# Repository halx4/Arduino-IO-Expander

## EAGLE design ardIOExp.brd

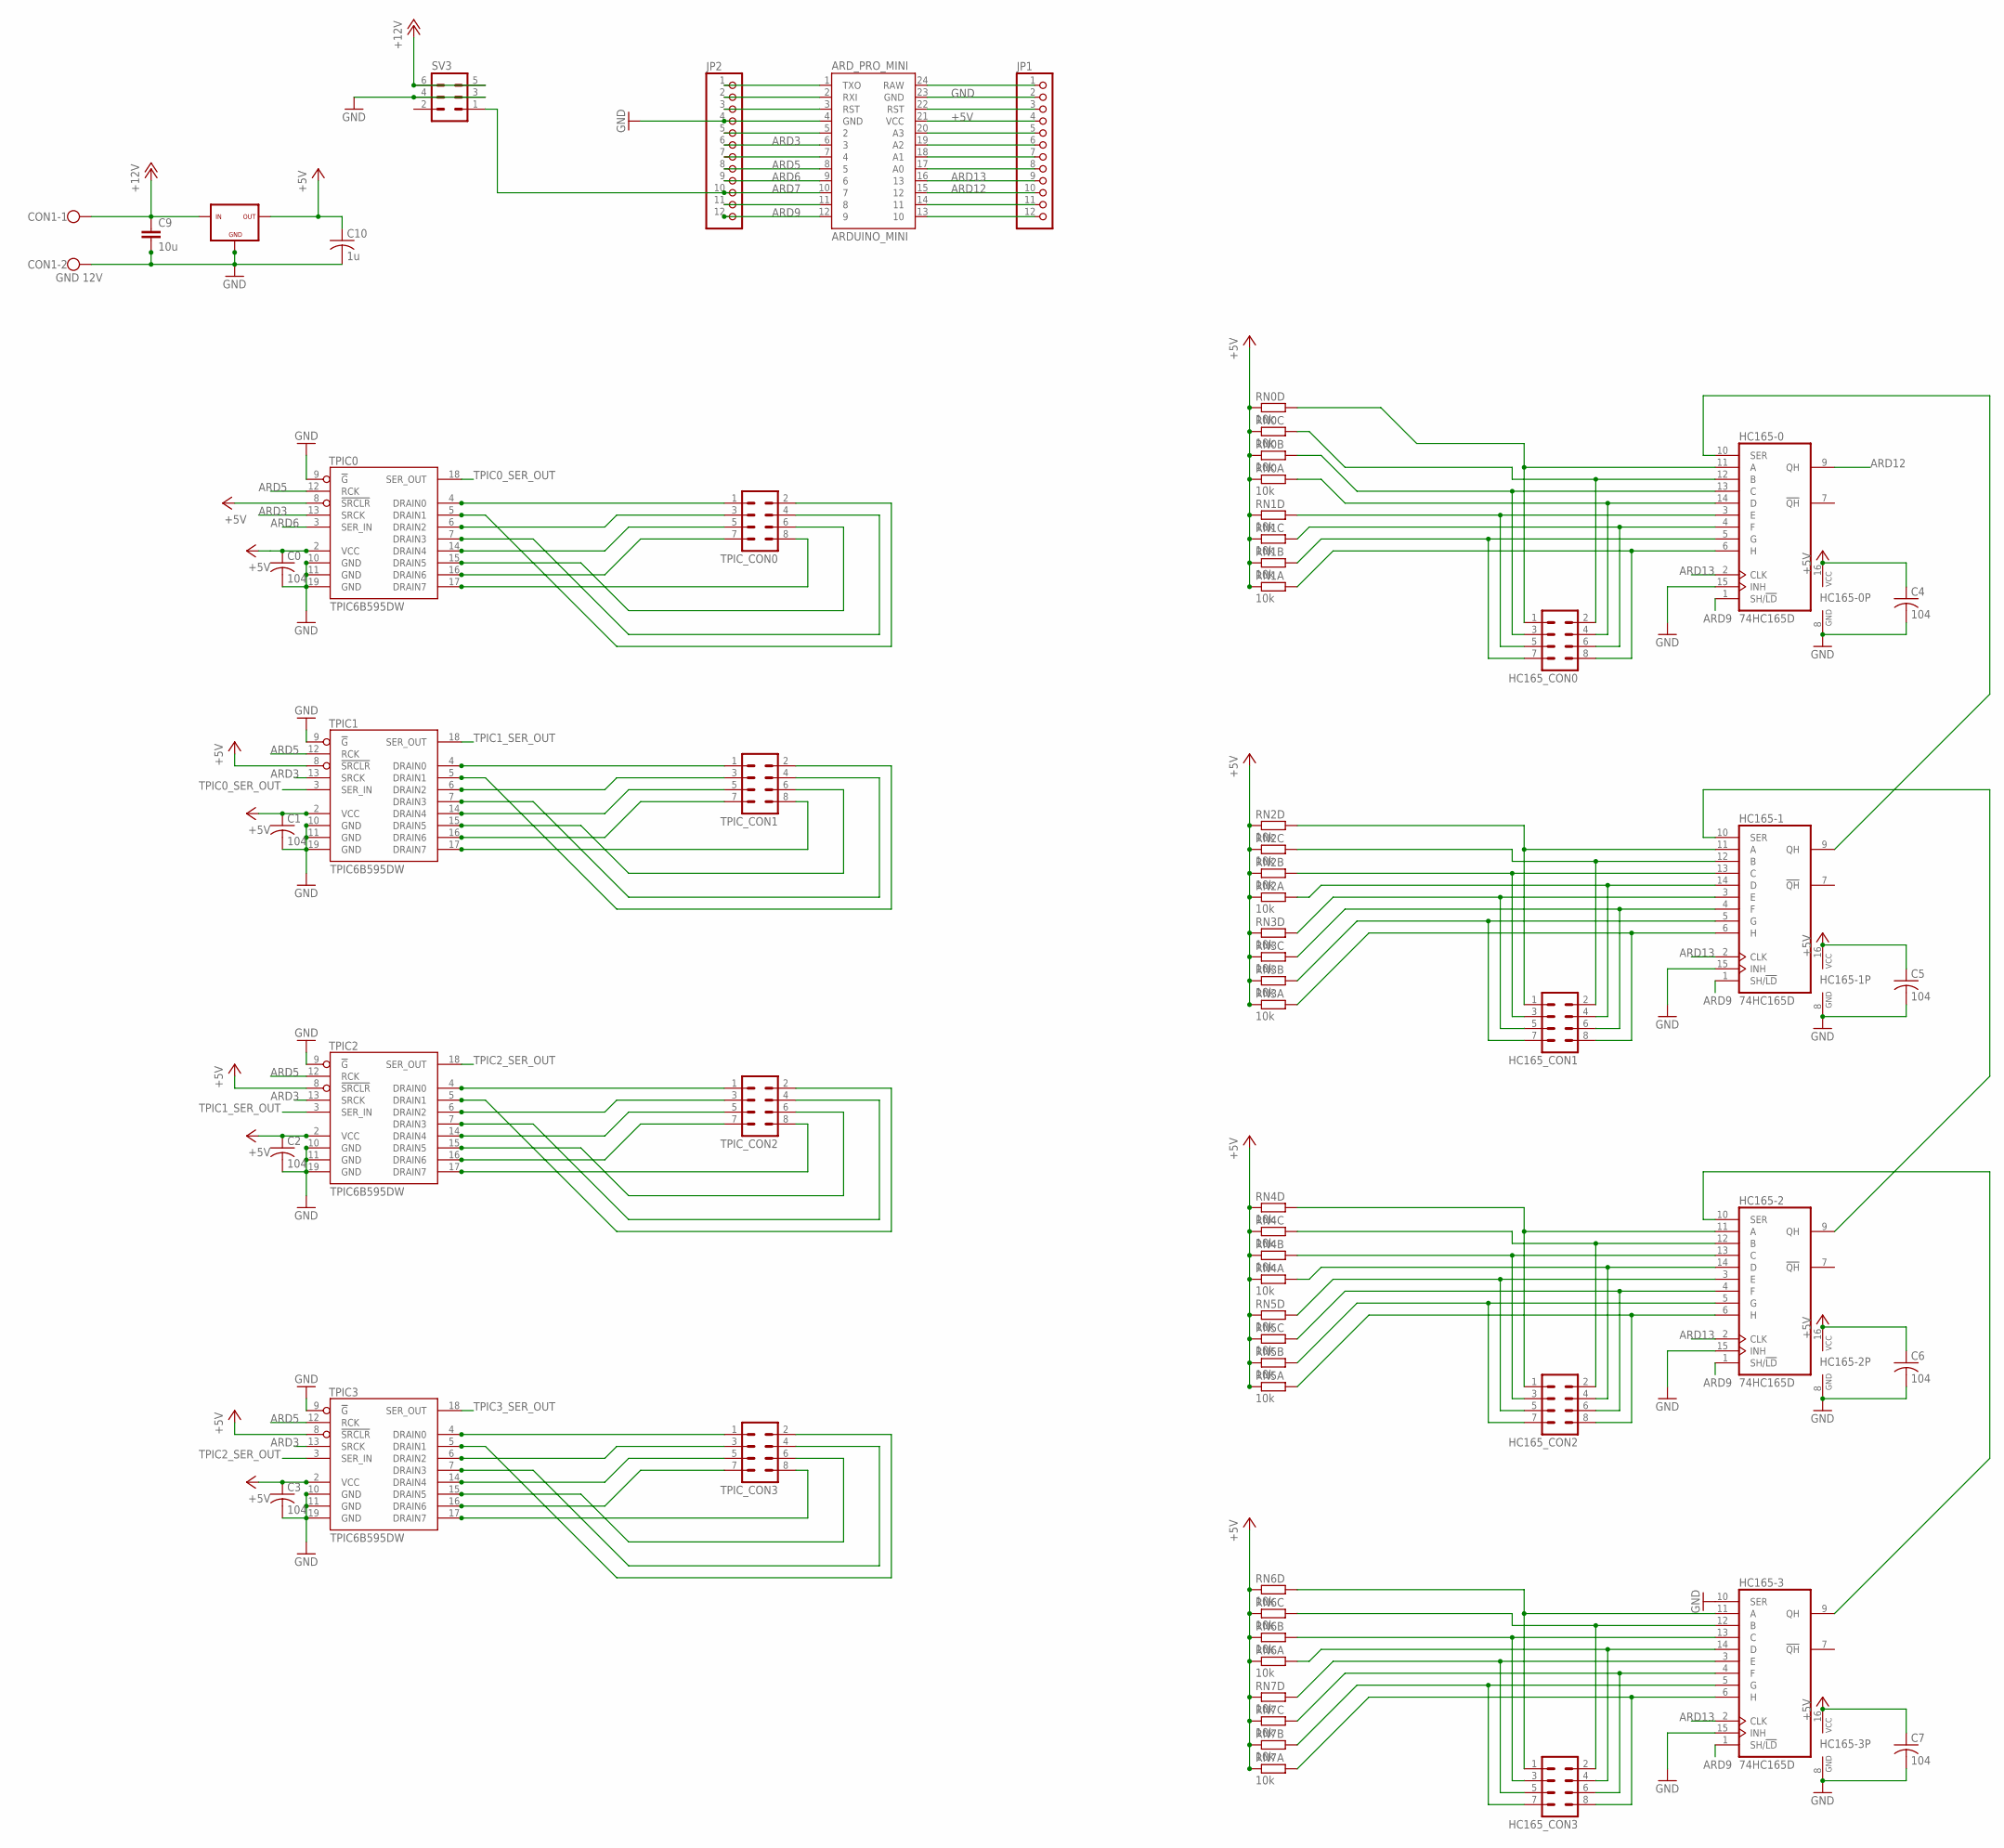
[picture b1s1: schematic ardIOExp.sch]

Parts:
ARD_PRO_MINI: ARDUINO_MINI
C0, C1, C2, C3, C4, C5, C6, C7: 104; C0603
C9: 10u; C050-024X044
C10: 1u; C0805
CON1: GND 12V; W237-102
HC165-0, HC165-1, HC165-2, HC165-3: 74HC165D; SO16
HC165_CON0, HC165_CON1, HC165_CON2, HC165_CON3: MA04-2
JP1, JP2: PINHD-1X12-CB; 1X12-CB
RN0, RN1, RN2, RN3, RN4, RN5, RN6, RN7: 10k; RN8P-4R-CRA06S
SV3: MA03-2
TPIC0, TPIC1, TPIC2, TPIC3: TPIC6B595DW; SO20W
TPIC_CON0, TPIC_CON1, TPIC_CON2, TPIC_CON3: MA04-2
V_REG_5V: L78D2TT; D2PAK

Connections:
+5V: ARD_PRO_MINI.21 (VCC), C0.1, C1.1, C2.1, C3.1, C4.1, C5.1, C6.1, C7.1, C10.1, HC165-0.16 (VCC), HC165-1.16 (VCC), HC165-2.16 (VCC), HC165-3.16 (VCC), JP1.4, RN0.1, RN0.2 (1), RN0.3 (1), RN0.4 (1), RN1.1, RN1.2 (1), RN1.3 (1), RN1.4 (1), RN2.1, RN2.2 (1), RN2.3 (1), RN2.4 (1), RN3.1, RN3.2 (1), RN3.3 (1), RN3.4 (1), RN4.1, RN4.2 (1), RN4.3 (1), RN4.4 (1), RN5.1, RN5.2 (1), RN5.3 (1), RN5.4 (1), RN6.1, RN6.2 (1), RN6.3 (1), RN6.4 (1), RN7.1, RN7.2 (1), RN7.3 (1), RN7.4 (1), TPIC0.2 (VCC), TPIC0.8 (!SRCLR), TPIC1.2 (VCC), TPIC1.8 (!SRCLR), TPIC2.2 (VCC), TPIC2.8 (!SRCLR), TPIC3.2 (VCC), TPIC3.8 (!SRCLR), V_REG_5V.3 (OUT)
+12V: C9.1, CON1.1, SV3.5, SV3.6, V_REG_5V.1 (IN)
ARD3: ARD_PRO_MINI.6 (3), JP2.6, TPIC0.13 (SRCK), TPIC1.13 (SRCK), TPIC2.13 (SRCK), TPIC3.13 (SRCK)
ARD5: ARD_PRO_MINI.8 (5), JP2.8, TPIC0.12 (RCK), TPIC1.12 (RCK), TPIC2.12 (RCK), TPIC3.12 (RCK)
ARD6: ARD_PRO_MINI.9 (6), JP2.9, TPIC0.3 (SER_IN)
ARD7: ARD_PRO_MINI.10 (7), JP2.10, SV3.1
ARD9: ARD_PRO_MINI.12 (9), HC165-0.1 (SH/!LD), HC165-1.1 (SH/!LD), HC165-2.1 (SH/!LD), HC165-3.1 (SH/!LD), JP2.12
ARD12: ARD_PRO_MINI.15 (12), HC165-0.9 (QH), JP1.10
ARD13: ARD_PRO_MINI.16 (13), HC165-0.2 (CLK), HC165-1.2 (CLK), HC165-2.2 (CLK), HC165-3.2 (CLK), JP1.9
GND: ARD_PRO_MINI.4 (GND), ARD_PRO_MINI.23 (GND), C0.2, C1.2, C2.2, C3.2, C4.2, C5.2, C6.2, C7.2, C9.2, C10.2, CON1.2, HC165-0.8 (GND), HC165-0.15 (INH), HC165-1.8 (GND), HC165-1.15 (INH), HC165-2.8 (GND), HC165-2.15 (INH), HC165-3.8 (GND), HC165-3.10 (SER), HC165-3.15 (INH), JP1.2, JP2.4, SV3.3, SV3.4, TPIC0.9 (!G), TPIC0.10 (GND), TPIC0.11 (GND), TPIC0.19 (GND), TPIC1.9 (!G), TPIC1.10 (GND), TPIC1.11 (GND), TPIC1.19 (GND), TPIC2.9 (!G), TPIC2.10 (GND), TPIC2.11 (GND), TPIC2.19 (GND), TPIC3.9 (!G), TPIC3.10 (GND), TPIC3.11 (GND), TPIC3.19 (GND), V_REG_5V.2 (GND)
unnamed: TPIC0.4 (DRAIN0), TPIC_CON0.1
unnamed: TPIC0.5 (DRAIN1), TPIC_CON0.2
unnamed: TPIC0.6 (DRAIN2), TPIC_CON0.3
unnamed: TPIC0.7 (DRAIN3), TPIC_CON0.4
unnamed: TPIC0.14 (DRAIN4), TPIC_CON0.5
unnamed: TPIC0.16 (DRAIN6), TPIC_CON0.7
unnamed: TPIC0.15 (DRAIN5), TPIC_CON0.6
unnamed: TPIC0.17 (DRAIN7), TPIC_CON0.8
unnamed: TPIC1.4 (DRAIN0), TPIC_CON1.1
unnamed: TPIC1.5 (DRAIN1), TPIC_CON1.2
unnamed: TPIC1.6 (DRAIN2), TPIC_CON1.3
unnamed: TPIC1.7 (DRAIN3), TPIC_CON1.4
unnamed: TPIC1.14 (DRAIN4), TPIC_CON1.5
unnamed: TPIC1.16 (DRAIN6), TPIC_CON1.7
unnamed: TPIC1.15 (DRAIN5), TPIC_CON1.6
unnamed: TPIC1.17 (DRAIN7), TPIC_CON1.8
unnamed: TPIC2.4 (DRAIN0), TPIC_CON2.1
unnamed: TPIC2.6 (DRAIN2), TPIC_CON2.3
unnamed: TPIC2.7 (DRAIN3), TPIC_CON2.4
unnamed: TPIC2.5 (DRAIN1), TPIC_CON2.2
unnamed: TPIC2.16 (DRAIN6), TPIC_CON2.7
unnamed: HC165-0.5 (G), HC165_CON0.7, RN1.7 (2)
unnamed: TPIC3.6 (DRAIN2), TPIC_CON3.3
unnamed: TPIC2.14 (DRAIN4), TPIC_CON2.5
unnamed: TPIC2.15 (DRAIN5), TPIC_CON2.6
unnamed: TPIC2.17 (DRAIN7), TPIC_CON2.8
unnamed: HC165-0.3 (E), HC165_CON0.5, RN1.5 (2)
unnamed: HC165-0.6 (H), HC165_CON0.8, RN1.8 (2)
unnamed: HC165-0.13 (C), HC165_CON0.3, RN0.7 (2)
unnamed: HC165-0.12 (B), HC165_CON0.2, RN0.6 (2)
unnamed: HC165-0.14 (D), HC165_CON0.4, RN0.8 (2)
unnamed: ARD_PRO_MINI.1 (TXO), JP2.1
unnamed: HC165-0.11 (A), HC165_CON0.1, RN0.5 (2)
unnamed: ARD_PRO_MINI.7 (4), JP2.7
unnamed: HC165-1.11 (A), HC165_CON1.1, RN2.5 (2)
unnamed: HC165-1.12 (B), HC165_CON1.2, RN2.6 (2)
unnamed: HC165-1.13 (C), HC165_CON1.3, RN2.7 (2)
unnamed: HC165-1.14 (D), HC165_CON1.4, RN2.8 (2)
unnamed: HC165-1.3 (E), HC165_CON1.5, RN3.5 (2)
unnamed: HC165-1.4 (F), HC165_CON1.6, RN3.6 (2)
unnamed: HC165-2.11 (A), HC165_CON2.1, RN4.5 (2)
unnamed: HC165-2.14 (D), HC165_CON2.4, RN4.8 (2)
unnamed: HC165-0.10 (SER), HC165-1.9 (QH)
unnamed: HC165-2.12 (B), HC165_CON2.2, RN4.6 (2)
unnamed: HC165-2.13 (C), HC165_CON2.3, RN4.7 (2)
unnamed: HC165-2.3 (E), HC165_CON2.5, RN5.5 (2)
unnamed: HC165-2.4 (F), HC165_CON2.6, RN5.6 (2)
unnamed: HC165-1.10 (SER), HC165-2.9 (QH)
unnamed: HC165-2.10 (SER), HC165-3.9 (QH)
unnamed: HC165-3.14 (D), HC165_CON3.4, RN6.8 (2)
unnamed: HC165-3.11 (A), HC165_CON3.1, RN6.5 (2)
unnamed: HC165-3.12 (B), HC165_CON3.2, RN6.6 (2)
unnamed: HC165-3.13 (C), HC165_CON3.3, RN6.7 (2)
unnamed: HC165-3.5 (G), HC165_CON3.7, RN7.7 (2)
unnamed: HC165-3.6 (H), HC165_CON3.8, RN7.8 (2)
unnamed: HC165-3.3 (E), HC165_CON3.5, RN7.5 (2)
unnamed: HC165-3.4 (F), HC165_CON3.6, RN7.6 (2)
unnamed: TPIC3.7 (DRAIN3), TPIC_CON3.4
unnamed: TPIC3.5 (DRAIN1), TPIC_CON3.2
unnamed: TPIC3.4 (DRAIN0), TPIC_CON3.1
unnamed: TPIC3.15 (DRAIN5), TPIC_CON3.6
unnamed: TPIC3.14 (DRAIN4), TPIC_CON3.5
unnamed: TPIC3.16 (DRAIN6), TPIC_CON3.7
unnamed: TPIC3.17 (DRAIN7), TPIC_CON3.8
unnamed: ARD_PRO_MINI.2 (RXI), JP2.2
unnamed: ARD_PRO_MINI.3 (RST), JP2.3
unnamed: ARD_PRO_MINI.5 (2), JP2.5
unnamed: HC165-1.5 (G), HC165_CON1.7, RN3.7 (2)
unnamed: ARD_PRO_MINI.11 (8), JP2.11
unnamed: ARD_PRO_MINI.24 (RAW), JP1.1
unnamed: ARD_PRO_MINI.22 (RST), JP1.3
unnamed: HC165-0.4 (F), HC165_CON0.6, RN1.6 (2)
unnamed: ARD_PRO_MINI.20 (A3), JP1.5
unnamed: ARD_PRO_MINI.19 (A2), JP1.6
unnamed: ARD_PRO_MINI.18 (A1), JP1.7
unnamed: ARD_PRO_MINI.17 (A0), JP1.8
unnamed: ARD_PRO_MINI.14 (11), JP1.11
unnamed: ARD_PRO_MINI.13 (10), JP1.12
unnamed: HC165-2.5 (G), HC165_CON2.7, RN5.7 (2)
unnamed: HC165-2.6 (H), HC165_CON2.8, RN5.8 (2)
unnamed: HC165-1.6 (H), HC165_CON1.8, RN3.8 (2)
TPIC0_SER_OUT: TPIC0.18 (SER_OUT), TPIC1.3 (SER_IN)
TPIC1_SER_OUT: TPIC1.18 (SER_OUT), TPIC2.3 (SER_IN)
TPIC2_SER_OUT: TPIC2.18 (SER_OUT), TPIC3.3 (SER_IN)
TPIC3_SER_OUT: TPIC3.18 (SER_OUT)

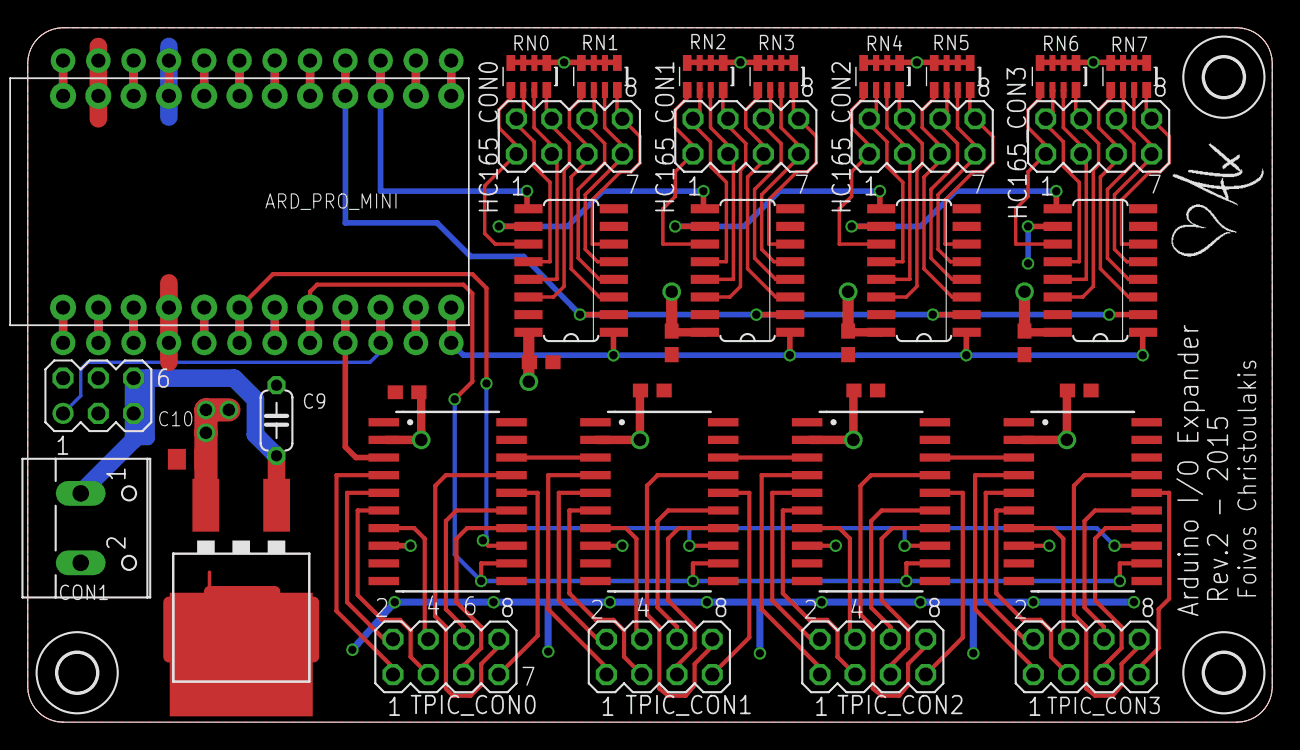
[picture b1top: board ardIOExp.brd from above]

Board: 2 copper layers, 89.6 x 50.0 mm, 45 parts (0 on the bottom side), 94 nets.

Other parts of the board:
U$1, U$3, U$4: 2,8
U$6: HALX2_532_SILKSCREEN
U$7: HALX2_532_TSTOP

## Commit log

2017-07-21 init commit
2017-07-22 change name of voltage regulator

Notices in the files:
parts and their libraries:
SparkFun-Boards: Licensing: Creative Commons ShareAlike 4.0 International - https://creativecommons.org/licenses/by-sa/4.0
